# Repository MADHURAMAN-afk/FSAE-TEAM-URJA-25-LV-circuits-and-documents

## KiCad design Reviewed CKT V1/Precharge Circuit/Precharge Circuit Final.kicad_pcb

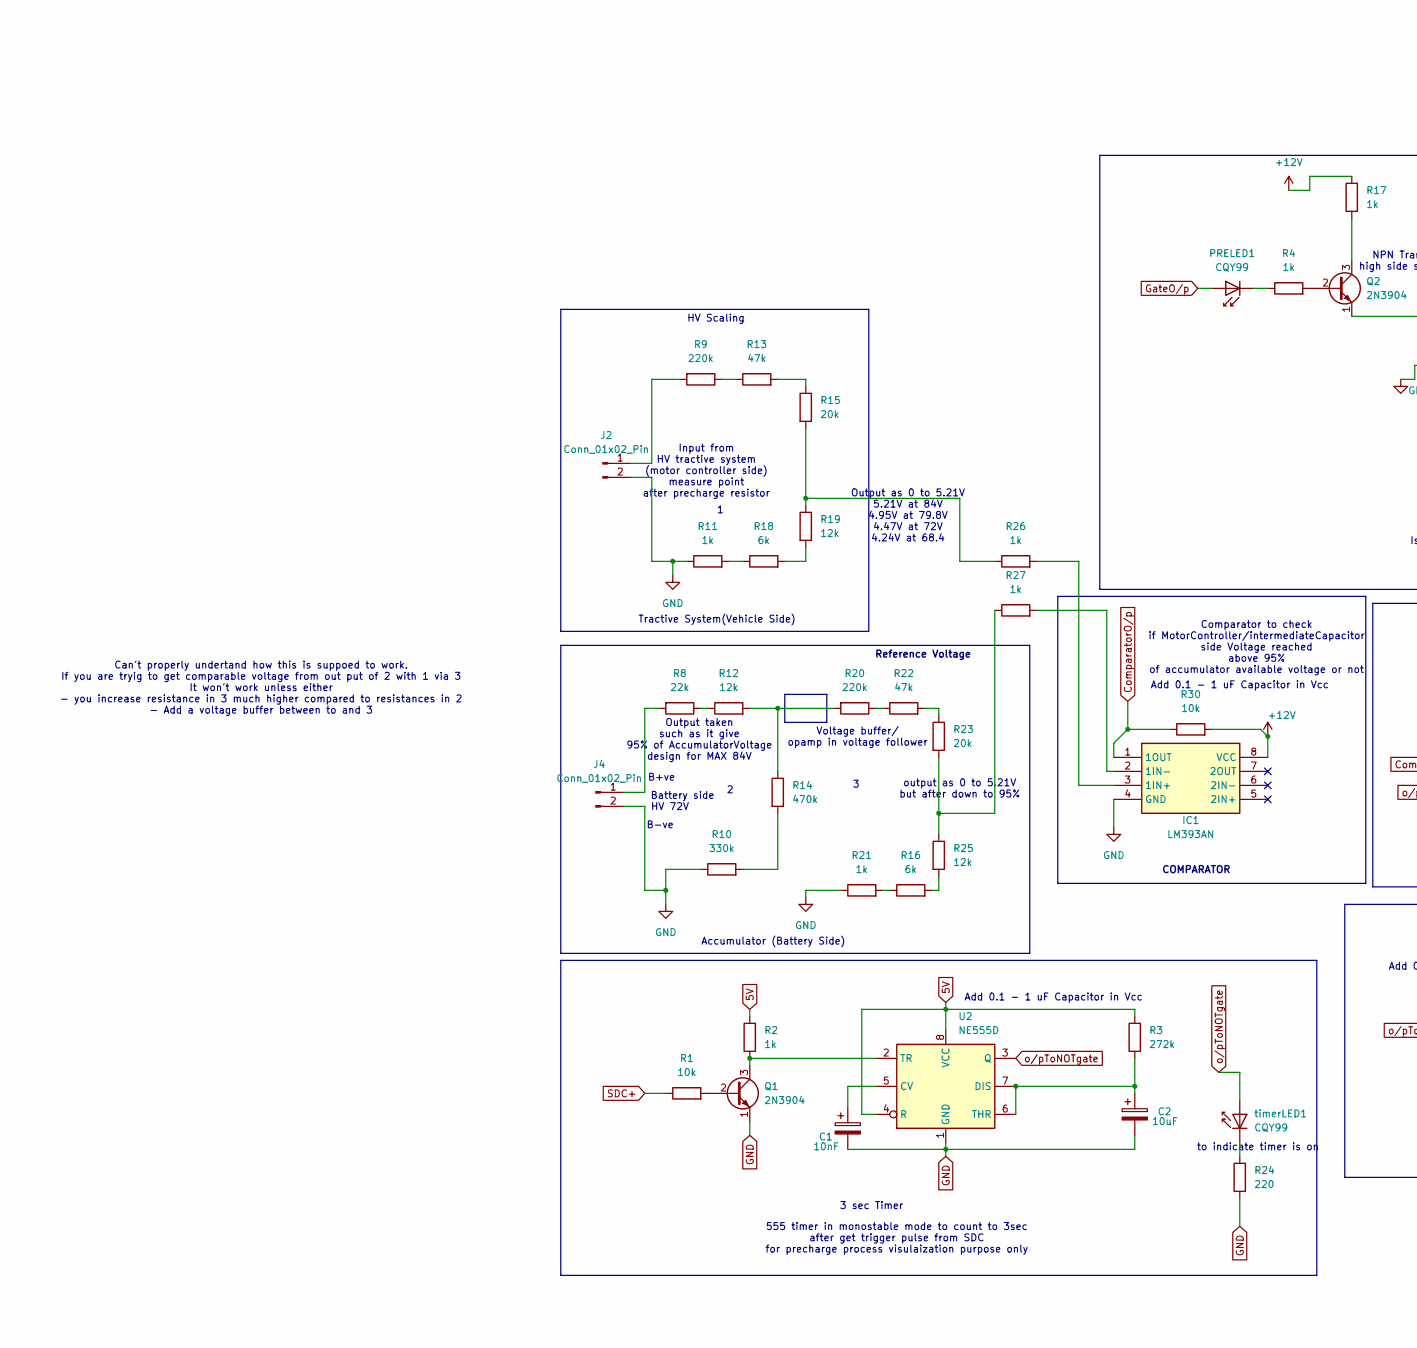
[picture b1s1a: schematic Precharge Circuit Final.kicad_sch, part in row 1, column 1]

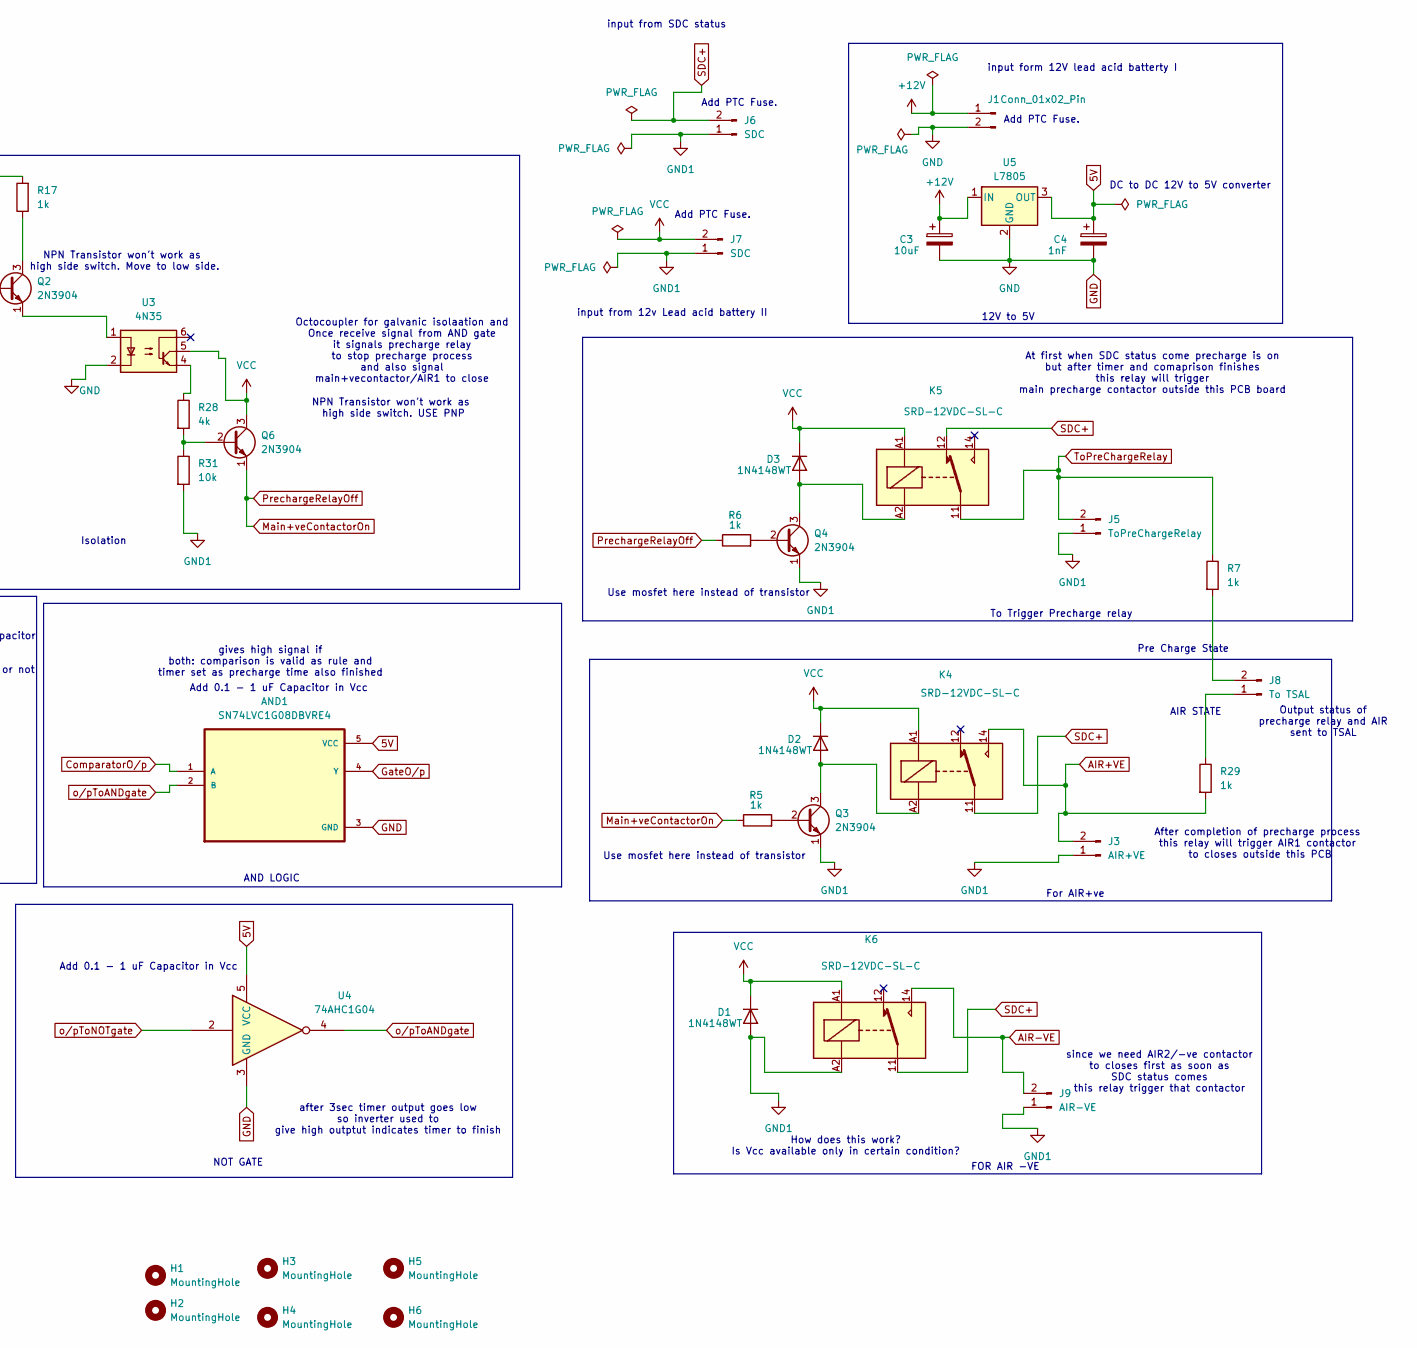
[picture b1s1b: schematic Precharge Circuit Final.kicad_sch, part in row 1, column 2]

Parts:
AND1: SN74LVC1G08DBVRE4; SOT95P280X145-5N
C1: 10nF; CP_Radial_D4.0mm_P2.00mm
C2, C3: 10uF; CP_Radial_D4.0mm_P2.00mm
C4: 1nF; CP_Radial_D4.0mm_P2.00mm
D1, D2, D3: 1N4148WT; D_A-405_P7.62mm_Horizontal
H1, H2, H3, H4, H5, H6: MountingHole; MountingHole_4.3mm_M4
IC1: LM393AN; DIP-8_W7.62mm_Socket; Manufacturer_Part_Number LM393AN; Mouser Part Number N/A
J1, J2, J4: Conn_01x02_Pin; TerminalBlock_Phoenix_MKDS-1,5-2-5.08_1x02_P5.08mm_Horizont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
J3: AIR+VE; TerminalBlock_Phoenix_MKDS-1,5-2-5.08_1x02_P5.08mm_Horizont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
J5: ToPreChargeRelay; TerminalBlock_Phoenix_MKDS-1,5-2-5.08_1x02_P5.08mm_Horizont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
J6, J7: SDC; TerminalBlock_Phoenix_MKDS-1,5-2-5.08_1x02_P5.08mm_Horizont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
J8: To TSAL; TerminalBlock_Phoenix_MKDS-1,5-2-5.08_1x02_P5.08mm_Horizont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
J9: AIR-VE; TerminalBlock_Phoenix_MKDS-1,5-2-5.08_1x02_P5.08mm_Horizont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
K4, K5, K6: SRD-12VDC-SL-C; Relay_SPDT_Hongfa_HF3F-L-xx-1ZL1T
PRELED1: CQY99; LED_D5.0mm_IRGrey
Q1, Q2, Q3, Q4, Q6: 2N3904; TO-92_Inline_Wide
R1, R30, R31: 10k; R_Axial_DIN0207_L6.3mm_D2.5mm_P10.16mm_Horizontal
R2, R4, R5, R6, R7, R11, R17, R21, R26, R27, R29: 1k; R_Axial_DIN0207_L6.3mm_D2.5mm_P10.16mm_Horizontal
R3: 272k; R_Axial_DIN0207_L6.3mm_D2.5mm_P10.16mm_Horizontal
R8: 22k; R_Axial_DIN0207_L6.3mm_D2.5mm_P10.16mm_Horizontal
R9, R20: 220k; R_Axial_DIN0207_L6.3mm_D2.5mm_P10.16mm_Horizontal
R10: 330k; R_Axial_DIN0207_L6.3mm_D2.5mm_P10.16mm_Horizontal
R12, R19, R25: 12k; R_Axial_DIN0207_L6.3mm_D2.5mm_P10.16mm_Horizontal
R13, R22: 47k; R_Axial_DIN0207_L6.3mm_D2.5mm_P10.16mm_Horizontal
R14: 470k; R_Axial_DIN0207_L6.3mm_D2.5mm_P10.16mm_Horizontal
R15, R23: 20k; R_Axial_DIN0207_L6.3mm_D2.5mm_P10.16mm_Horizontal
R16, R18: 6k; R_Axial_DIN0207_L6.3mm_D2.5mm_P10.16mm_Horizontal
R24: 220; R_Axial_DIN0207_L6.3mm_D2.5mm_P10.16mm_Horizontal
R28: 4k; R_Axial_DIN0207_L6.3mm_D2.5mm_P10.16mm_Horizontal
U2: NE555D; DIP-8_W7.62mm
U3: 4N35; DIP-6_W7.62mm
U4: 74AHC1G04; SOT-23-5
U5: L7805; TO-220-3_Vertical
timerLED1: CQY99; LED_D5.0mm_IRGrey

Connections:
5V: AND1.5 (VCC), C4.1, R2.2, R3.2, U2.4 (R), U2.8 (VCC), U4.5 (VCC), U5.3 (OUT)
+12V: C3.1, IC1.8 (VCC), J1.1, R17.2, R30.2, U5.1 (IN)
AIR+VE: J3.2, K4.14, R29.2
AIR-VE: J9.2, K6.14
ComparatorO/p: AND1.1 (A), IC1.1 (1OUT), R30.1
GND: AND1.3 (GND), C1.2, C2.2, C3.2, C4.2, IC1.4 (GND), J1.2, J2.2, J4.2, Q1.1 (E), R10.1, R11.1, R21.1, R24.1, U2.1 (GND), U3.2, U4.3 (GND), U5.2 (GND)
GND1: D1.2 (A), J3.1, J5.1, J6.1, J7.1, J9.1, K6.A2, Q3.1 (E), Q4.1 (E), R31.2
GateO/p: AND1.4 (Y), PRELED1.2 (A)
Main+veContactorOn: Q6.1 (E), R5.1, R6.1
unnamed: D2.2 (A), K4.A2, Q3.3 (C)
unnamed: D3.2 (A), K5.A2, Q4.3 (C)
unnamed: IC1.3 (1IN+), R26.2
unnamed: IC1.2 (1IN-), R27.2
unnamed: J2.1, R9.2
unnamed: J4.1, R8.2
unnamed: J8.1, R29.1
unnamed: J8.2, R7.2
unnamed: PRELED1.1 (K), R4.1
unnamed: Q1.2 (B), R1.2
unnamed: Q1.3 (C), R2.1, U2.2 (TR)
unnamed: Q2.2 (B), R4.2
unnamed: Q2.3 (C), R17.1
unnamed: Q2.1 (E), U3.1
unnamed: Q3.2 (B), R5.2
unnamed: Q4.2 (B), R6.2
unnamed: Q6.2 (B), R28.2, R31.1
unnamed: R10.2, R14.2
unnamed: R11.2, R18.1
unnamed: R8.1, R12.1
unnamed: R12.2, R14.1, R20.2
unnamed: R9.1, R13.1
unnamed: R13.2, R15.1
unnamed: R15.2, R19.1, R26.1
unnamed: R16.1, R21.2
unnamed: R16.2, R25.2
unnamed: R18.2, R19.2
unnamed: R20.1, R22.1
unnamed: R22.2, R23.1
unnamed: R23.2, R25.1, R27.1
unnamed: R28.1, U3.4
unnamed: C1.1, U2.5 (CV)
unnamed: C2.1, R3.1, U2.6 (THR), U2.7 (DIS)
unnamed: R24.2, timerLED1.1 (K)
SDC+: J6.2, K4.11, K5.12, K6.11, R1.1
ToPreChargeRelay: J5.2, K5.11, R7.1
VCC: D1.1 (K), D2.1 (K), D3.1 (K), J7.2, K4.A1, K5.A1, K6.A1, Q6.3 (C), U3.5
o/pToANDgate: AND1.2 (B), U4.4
o/pToNOTgate: U2.3 (Q), U4.2, timerLED1.2 (A)

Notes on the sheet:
since we need AIR2/-ve contactor to closes first as soon as SDC status comes this relay trigger that contactor
B+ve
FOR AIR -VE
After completion of precharge process this relay will trigger AIR1 contactor to closes outside this PCB
Output taken such as it give 95% of AccumulatorVoltage design for MAX 84V
B-ve
Battery side
output as 0 to 5.21V but after down to 95%
Add PTC Fuse.
NPN Transistor won't work as high side switch. USE PNP
COMPARATOR
Output status of precharge relay and AIR sent to TSAL
input from SDC status
NOT GATE
Comparator to check if MotorController/intermediateCapacitor side Voltage reached above 95% of accumulator available voltage or not
Isolation
How does this work? Is Vcc available only in certain condition?
At first when SDC status come precharge is on but after timer and comaprison finishes this relay will trigger main precharge contactor outside this PCB board
NPN Transistor won't work as high side switch. Move to low side.
Use mosfet here instead of transistor
3 sec Timer
after 3sec timer output goes low so inverter used to give high outptut indicates timer to finish
Reference Voltage
Pre Charge State
12V to 5V
555 timer in monostable mode to count to 3sec after get trigger pulse from SDC for precharge process visulaization purpose only
gives high signal if both: comparison is valid as rule and timer set as precharge time also finished
input form 12V lead acid batterty I
Output as 0 to 5.21V 5.21V at 84V 4.95V at 79.8V 4.47V at 72V 4.24V at 68.4
Add 0.1 - 1 uF Capacitor in Vcc
AIR STATE
DC to DC 12V to 5V converter
Tractive System(Vehicle Side)
HV 72V
Octocoupler for galvanic isolaation and Once receive signal from AND gate it signals precharge relay to stop precharge process and also signal main+vecontactor/AIR1 to close
Voltage buffer/ opamp in voltage follower
HV Scaling
Input from HV tractive system (motor controller side) measure point after precharge resistor
For AIR+ve
AND LOGIC

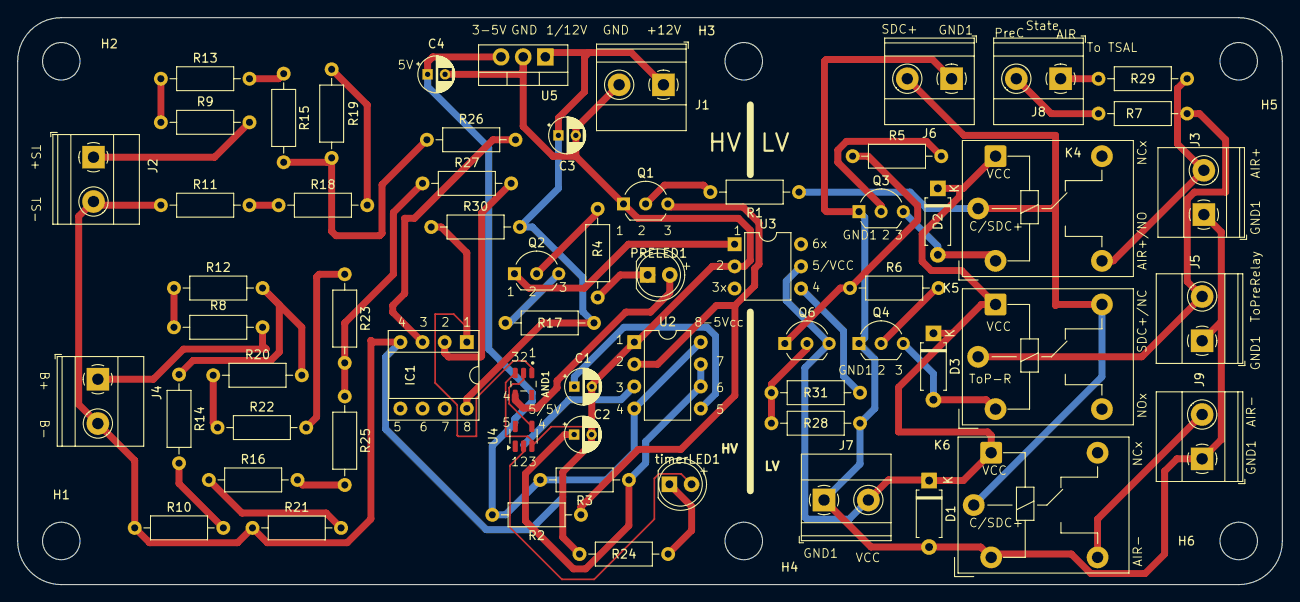
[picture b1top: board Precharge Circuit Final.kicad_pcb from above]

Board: 2 copper layers, 145.0 x 65.0 mm, 69 parts (0 on the bottom side), 48 nets.

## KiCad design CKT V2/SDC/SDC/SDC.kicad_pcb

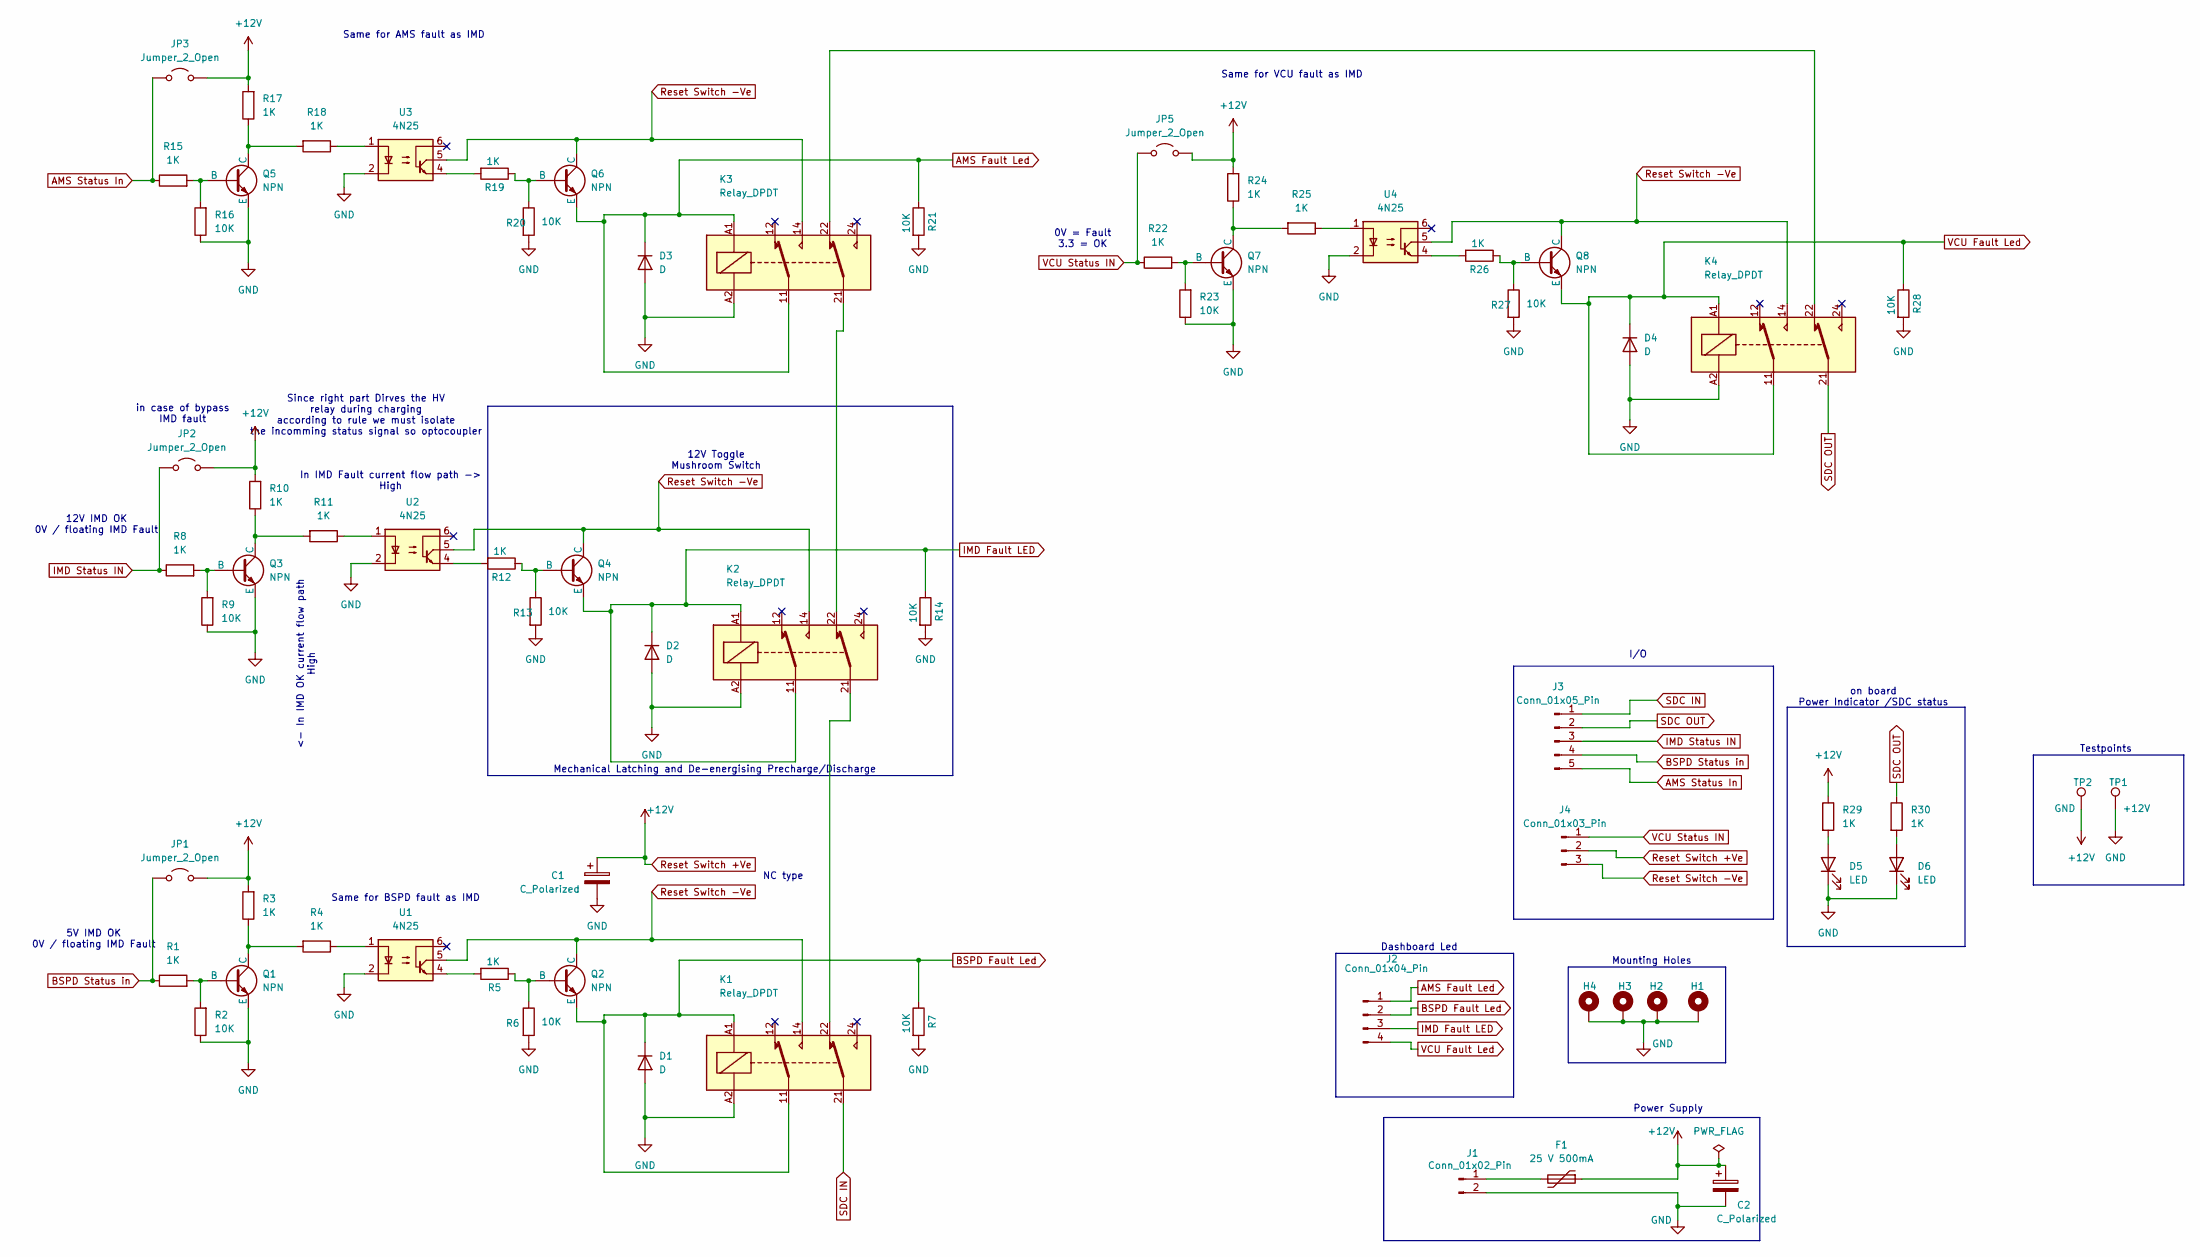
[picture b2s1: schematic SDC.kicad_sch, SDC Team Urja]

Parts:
C1, C2: C_Polarized; CP_Radial_D12.5mm_P7.50mm
D1, D2, D3, D4: D; D_A-405_P7.62mm_Horizontal
D5, D6: LED; LED_D4.0mm
F1: 25 V 500mA; Fuse_BelFuse_0ZRE0008FF_L8.3mm_W3.8mm
H1, H2, H3, H4: MountingHole_Pad; MountingHole_3.2mm_M3_ISO7380_Pad
J1: Conn_01x02_Pin; PinHeader_1x02_P2.54mm_Vertical
J2: Conn_01x04_Pin; PinHeader_1x04_P2.54mm_Vertical
J3: Conn_01x05_Pin; PinHeader_1x05_P2.54mm_Vertical
J4: Conn_01x03_Pin; PinHeader_1x03_P2.54mm_Vertical
JP1, JP2, JP3, JP5: Jumper_2_Open; PinHeader_1x02_P2.54mm_Vertical
K1, K2, K3, K4: Relay_DPDT; Relay_DPDT_Finder_40.52
Q1: NPN; TO-92L_Inline_Wide
Q2, Q3, Q4, Q5, Q6, Q7, Q8: NPN; TO-92_Inline_Wide
R1, R3, R4, R5, R8, R10, R11, R12, R15, R17, R18, R19, R22, R24, R25, R26, R29, R30: 1K; R_Axial_DIN0207_L6.3mm_D2.5mm_P7.62mm_Horizontal
R2, R6, R7, R9, R13, R14, R16, R20, R21, R23, R27, R28: 10K; R_Axial_DIN0207_L6.3mm_D2.5mm_P7.62mm_Horizontal
TP1: +12V; TestPoint_Pad_1.0x1.0mm
TP2: GND; TestPoint_Pad_1.0x1.0mm
U1, U2, U3, U4: 4N25; DIP-6_W7.62mm

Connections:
AMS Fault Led: D3.1 (K), J2.1, K3.11, K3.A1, Q6.3 (E), R21.1
AMS Status In: J3.5, JP3.1 (A), R15.1
BSPD Fault Led: D1.1 (K), J2.2, K1.11, K1.A1, Q2.3 (E), R7.1
BSPD Status in: J3.4, JP1.1 (A), R1.1
GND: C1.2, C2.2, D1.2 (A), D2.2 (A), D3.2 (A), D4.2 (A), D5.1 (K), D6.1 (K), H1.1, H2.1, H3.1, H4.1, J1.2, K1.A2, K2.A2, K3.A2, K4.A2, Q1.3 (E), Q3.3 (E), Q5.3 (E), Q7.3 (E), R2.1, R6.2, R7.2, R9.1, R13.2, R14.2, R16.1, R20.2, R21.2, R23.1, R27.2, R28.2, TP1.1, U1.2, U2.2, U3.2, U4.2
IMD Fault LED: D2.1 (K), J2.3, K2.11, K2.A1, Q4.3 (E), R14.1
IMD Status IN: J3.3, JP2.1 (A), R8.1
unnamed: D5.2 (A), R29.2
unnamed: D6.2 (A), R30.2
unnamed: F1.2, J1.1
unnamed: K1.22, K2.21
unnamed: K2.22, K3.21
unnamed: K3.22, K4.22
unnamed: Q1.2 (B), R1.2, R2.2
unnamed: Q1.1 (C), R3.1, R4.2
unnamed: Q2.2 (B), R5.1, R6.1
unnamed: Q3.2 (B), R8.2, R9.2
unnamed: Q3.1 (C), R10.1, R11.2
unnamed: Q4.2 (B), R12.1, R13.1
unnamed: Q5.2 (B), R15.2, R16.2
unnamed: Q5.1 (C), R17.1, R18.2
unnamed: Q6.2 (B), R19.1, R20.1
unnamed: Q7.2 (B), R22.2, R23.2
unnamed: Q7.1 (C), R24.1, R25.2
unnamed: Q8.2 (B), R26.1, R27.1
unnamed: R4.1, U1.1
unnamed: R5.2, U1.4
unnamed: R11.1, U2.1
unnamed: R12.2, U2.4
unnamed: R18.1, U3.1
unnamed: R19.2, U3.4
unnamed: R25.1, U4.1
unnamed: R26.2, U4.4
Reset Switch +Ve: C1.1, C2.1, F1.1, J4.2, JP1.2 (B), JP2.2 (B), JP3.2 (B), JP5.2 (B), R3.2, R10.2, R17.2, R24.2, R29.1, TP2.1
Reset Switch -Ve: J4.3, K1.14, K2.14, K3.14, K4.14, Q2.1 (C), Q4.1 (C), Q6.1 (C), Q8.1 (C), U1.5, U2.5, U3.5, U4.5
SDC IN: J3.1, K1.21
SDC OUT: J3.2, K4.21, R30.1
VCU Fault Led: D4.1 (K), J2.4, K4.11, K4.A1, Q8.3 (E), R28.1
VCU Status IN: J4.1, JP5.1 (A), R22.1

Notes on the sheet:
NC type
I/O
Dashboard Led
0V = Fault 3.3 = OK
5V IMD OK 0V / floating IMD Fault
Power Supply
12V Toggle Mushroom Switch
Same for VCU fault as IMD
Mounting Holes
on board Power Indicator /SDC status
Since right part Dirves the HV relay during charging according to rule we must isolate the incomming status signal so optocoupler
Testpoints
In IMD Fault current flow path -> High
12V IMD OK 0V / floating IMD Fault
Same for BSPD fault as IMD
Mechanical Latching and De-energising Precharge/Discharge
Same for AMS fault as IMD
<- In IMD OK current flow path High
in case of bypass IMD fault

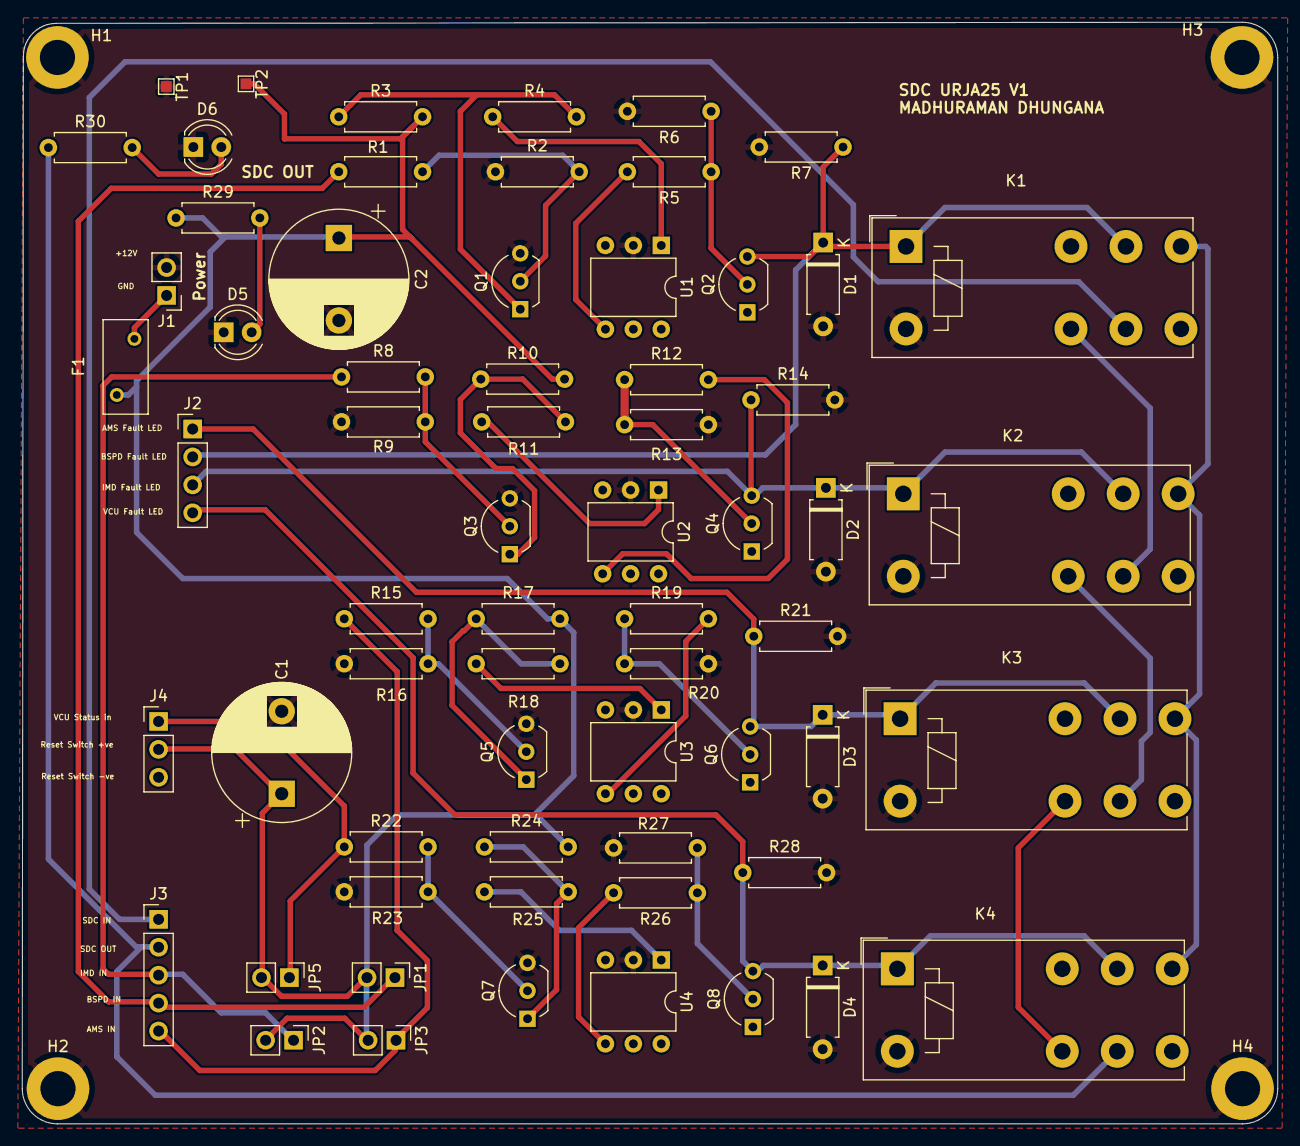
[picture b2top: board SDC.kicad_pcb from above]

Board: 2 copper layers, 114.2 x 100.2 mm, 69 parts (0 on the bottom side), 39 nets.

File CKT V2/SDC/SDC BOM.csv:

Reference,Value,Qty,DNP
"C1,C2",C_Polarized,2,
"D1,D2,D3,D4",D,4,
"D5,D6",LED,2,
F1,25 V 500mA,1,
J1,Conn_01x02_Pin,1,
J2,Conn_01x04_Pin,1,
J3,Conn_01x05_Pin,1,
J4,Conn_01x03_Pin,1,
"JP1,JP2,JP3,JP5",Jumper_2_Open,4,
"K1,K2,K3,K4",Relay_DPDT,4,
"Q1,Q2,Q3,Q4,Q5,Q6,Q7,Q8",NPN,8,
"R1,R3,R4,R5,R8,R10,R11,R12,R15,R17,R18,R19,R22,R24,R25,R26,R29,R30",1K,18,
"R2,R6,R7,R9,R13,R14,R16,R20,R21,R23,R27,R28",10K,12,
TP1,+12V,1,
TP2,GND,1,
"U1,U2,U3,U4",4N25,4,

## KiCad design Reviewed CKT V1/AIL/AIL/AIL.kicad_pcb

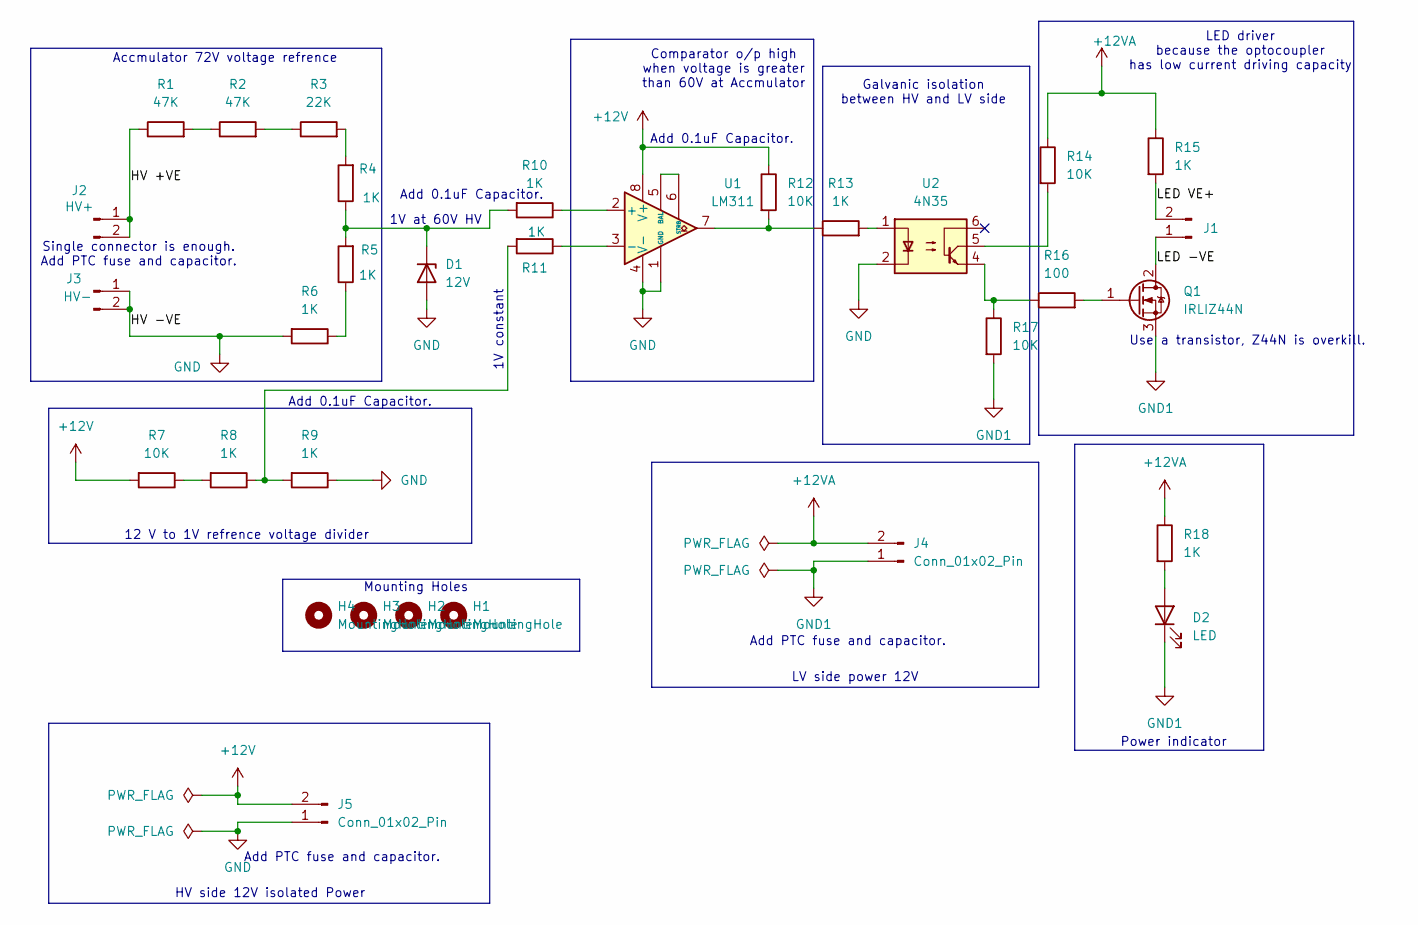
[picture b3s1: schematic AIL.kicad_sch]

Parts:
D1: 12V; D_A-405_P10.16mm_Horizontal
D2: LED; LED_D5.0mm
H1, H2, H3, H4: MountingHole; MountingHole_4.3mm_M4
J1, J4, J5: Conn_01x02_Pin; TerminalBlock_Phoenix_MKDS-1,5-2-5.08_1x02_P5.08mm_Horizont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
J2: HV+; TerminalBlock_Phoenix_MKDS-1,5-2-5.08_1x02_P5.08mm_Horizont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
J3: HV-; TerminalBlock_Phoenix_MKDS-1,5-2-5.08_1x02_P5.08mm_Horizont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
Q1: IRLIZ44N; TO-220F-3_Vertical
R1, R2: 47K; R_Axial_DIN0204_L3.6mm_D1.6mm_P7.62mm_Horizontal
R3: 22K; R_Axial_DIN0204_L3.6mm_D1.6mm_P7.62mm_Horizontal
R4, R5, R6, R8, R9, R10, R11, R13, R15, R18: 1K; R_Axial_DIN0204_L3.6mm_D1.6mm_P7.62mm_Horizontal
R7, R12, R14, R17: 10K; R_Axial_DIN0204_L3.6mm_D1.6mm_P7.62mm_Horizontal
R16: 100; R_Axial_DIN0204_L3.6mm_D1.6mm_P7.62mm_Horizontal
U1: LM311; CERDIP-8_W7.62mm_SideBrazed_LongPads
U2: 4N35; DIP-6_W7.62mm

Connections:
+12V: J5.2, R7.2, R12.1, U1.8 (V+)
+12VA: J4.2, R14.1, R15.1, R18.1
/HV +VE: J2.1, J2.2, R1.1
/LED -VE: J1.1, Q1.2 (D)
/LED VE+: J1.2, R15.2
GND: D1.2 (A), J3.1, J3.2, J5.1, R6.2, R9.1, U1.1 (GND), U1.4 (V-), U2.2
GND1: D2.1 (K), J4.1, Q1.3 (S), R17.2
unnamed: D1.1 (K), R4.1, R5.2, R10.2
unnamed: D2.2 (A), R18.2
unnamed: Q1.1 (G), R16.2
unnamed: R1.2, R2.1
unnamed: R2.2, R3.1
unnamed: R3.2, R4.2
unnamed: R5.1, R6.1
unnamed: R7.1, R8.2
unnamed: R8.1, R9.2, R11.2
unnamed: R12.2, R13.1, U1.7
unnamed: R13.2, U2.1
unnamed: R14.2, U2.5
unnamed: R16.1, R17.1, U2.4
unnamed: R10.1, U1.2 (+)
unnamed: R11.1, U1.3 (-)
unnamed: U1.5 (BAL), U1.6 (STRB)

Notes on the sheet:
12 V to 1V refrence voltage divider
Use a transistor, Z44N is overkill.
Add 0.1uF Capacitor.
1V at 60V HV
Power indicator
Galvanic isolation between HV and LV side
Comparator o/p high when voltage is greater than 60V at Accmulator
Accmulator 72V voltage refrence
Add PTC fuse and capacitor.
1V constant
LV side power 12V
Mounting Holes
HV side 12V isolated Power
Single connector is enough. Add PTC fuse and capacitor.
LED driver because the optocoupler has low current driving capacity

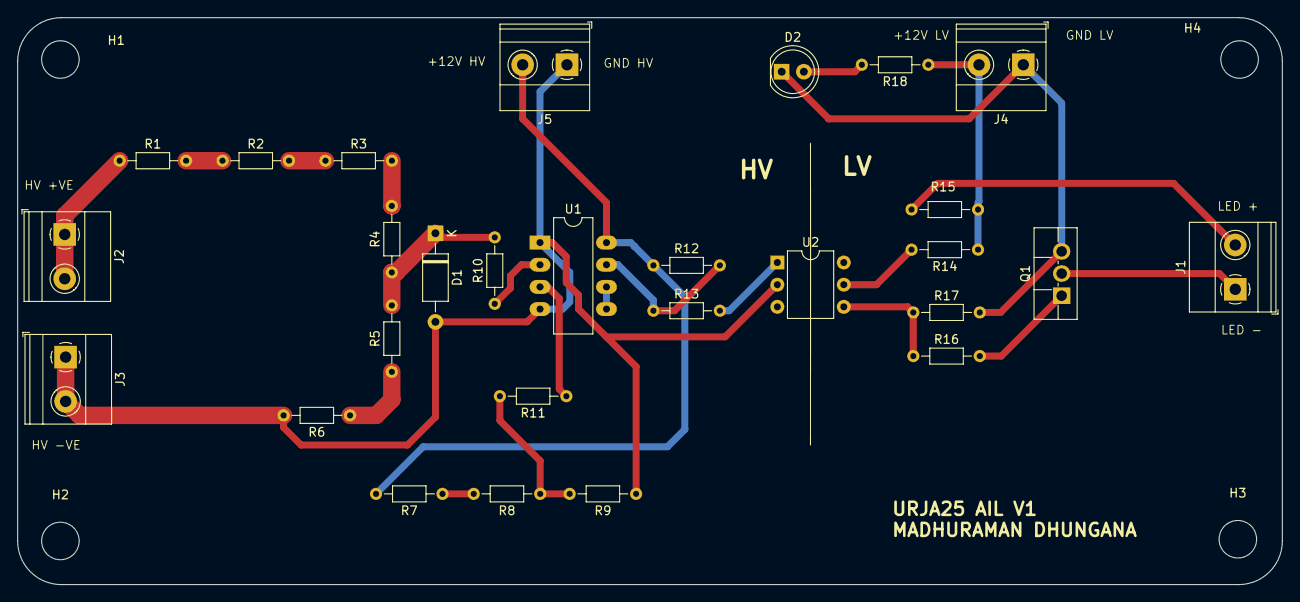
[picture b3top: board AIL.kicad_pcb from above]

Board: 2 copper layers, 145.0 x 65.0 mm, 32 parts (0 on the bottom side), 23 nets.

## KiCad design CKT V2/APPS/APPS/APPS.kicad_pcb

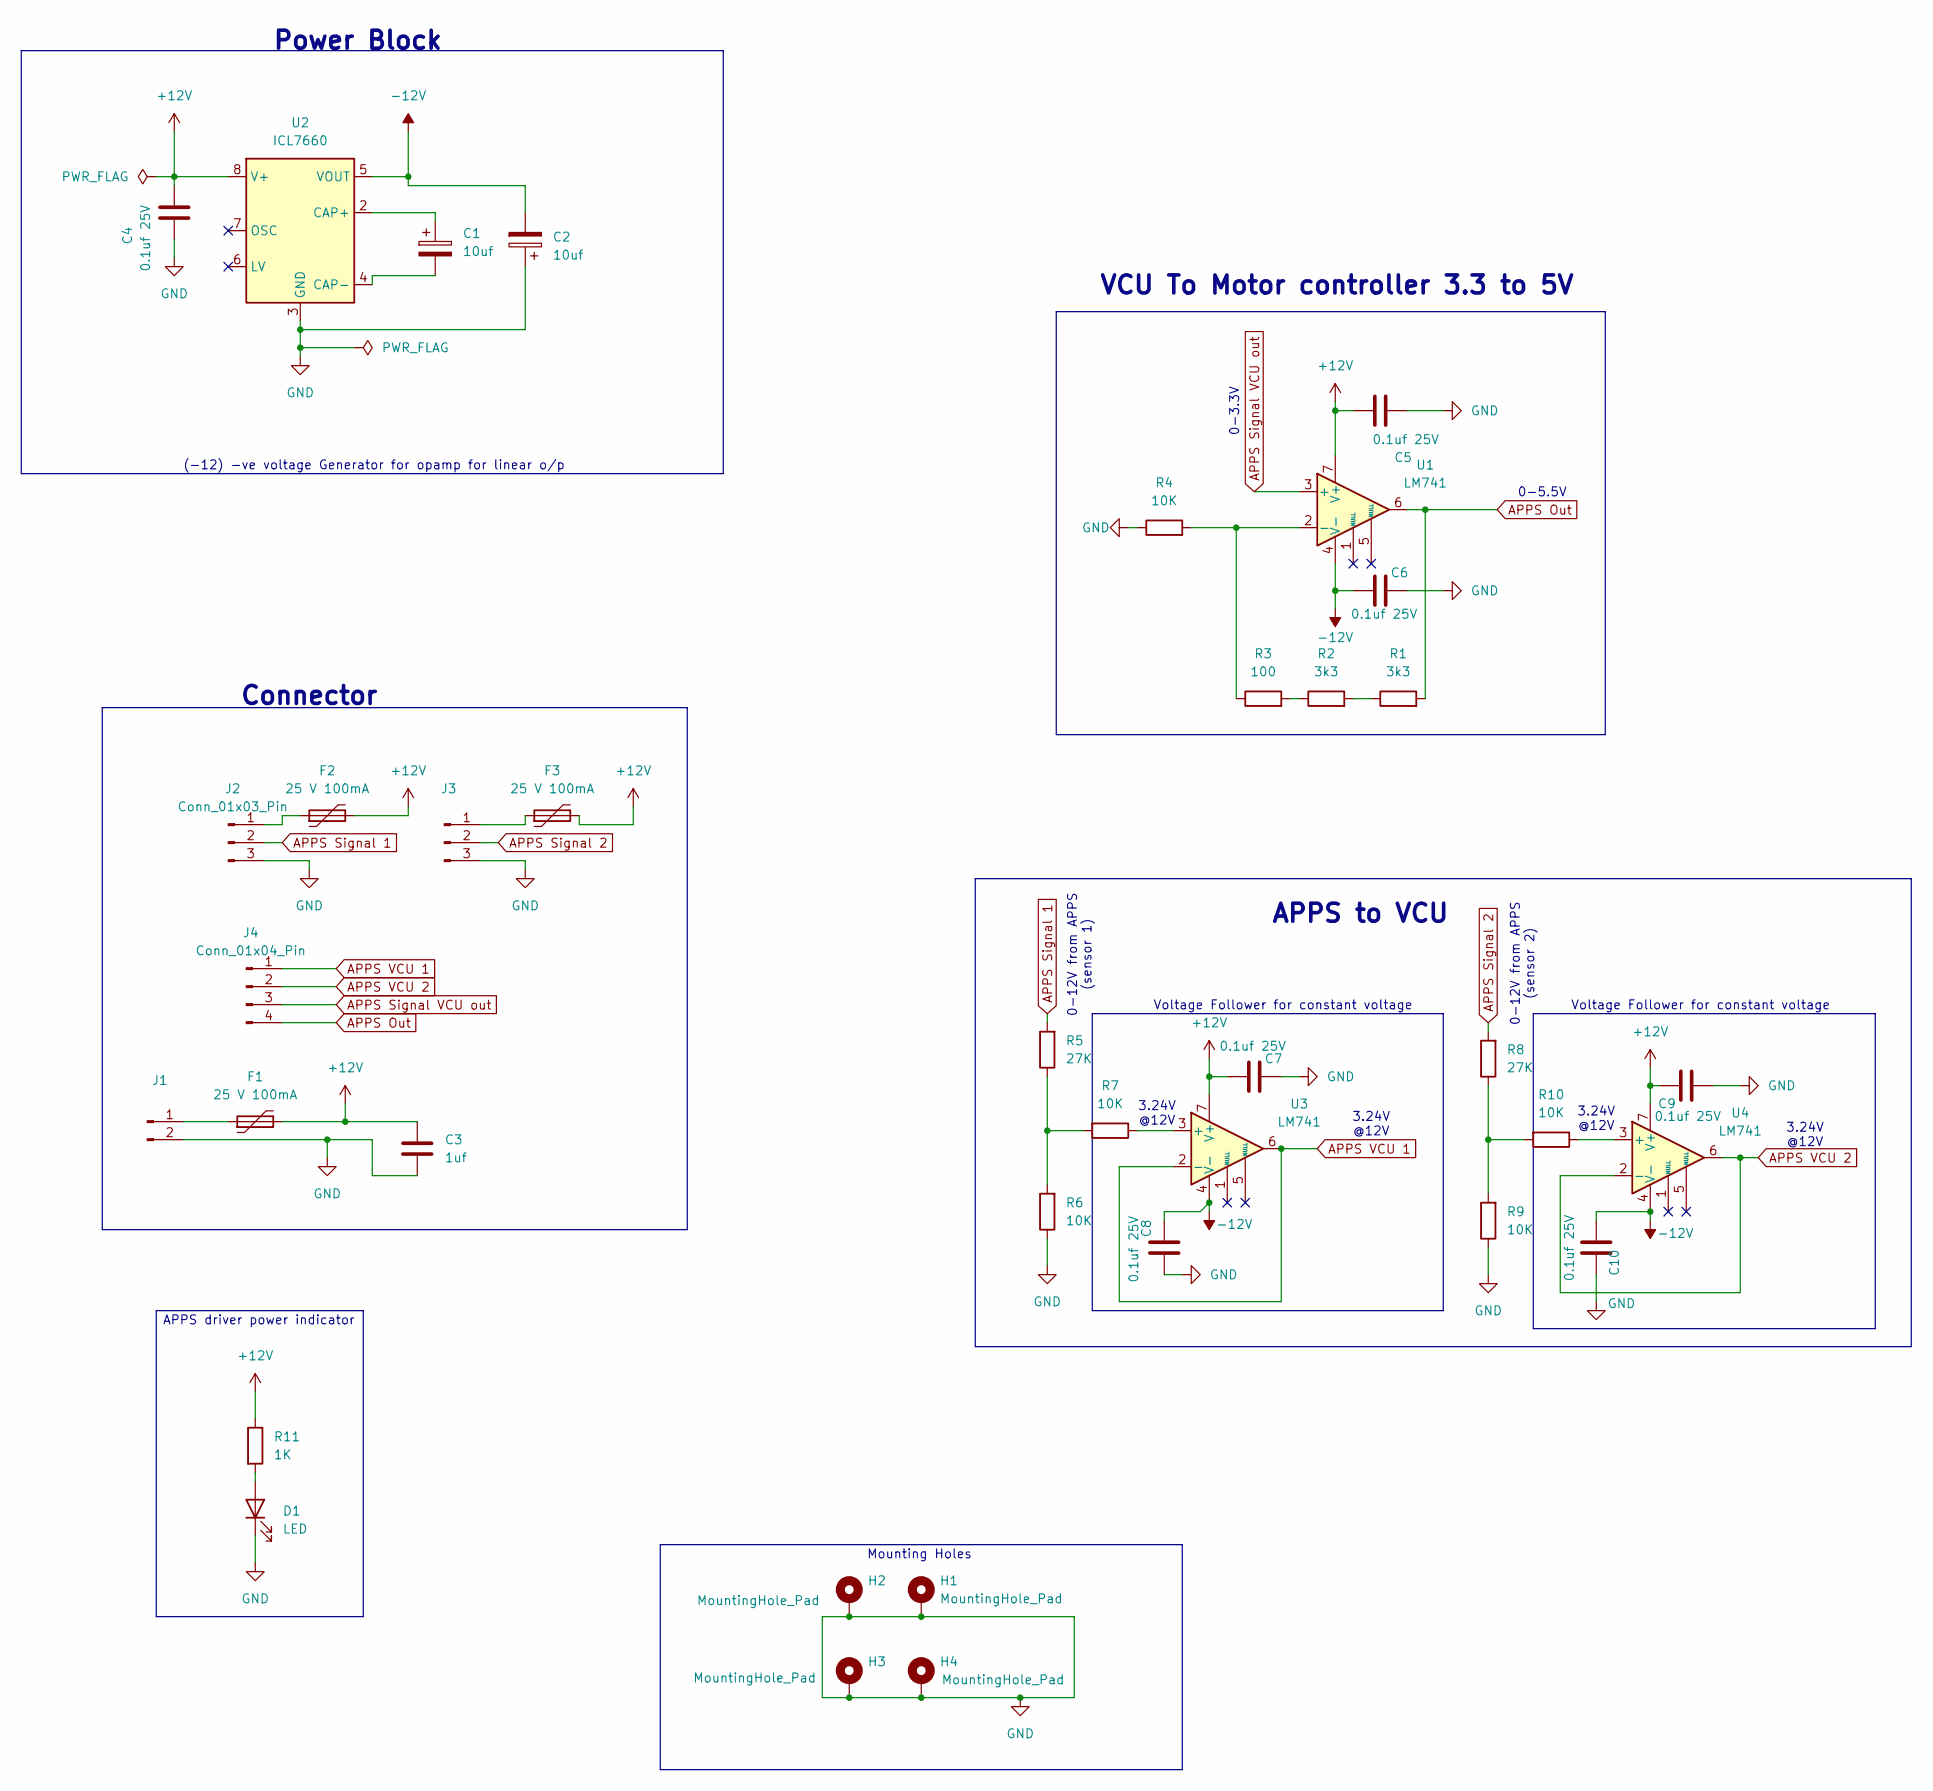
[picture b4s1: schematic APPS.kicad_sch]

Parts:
C1, C2: 10uf; CP_Radial_D8.0mm_P5.00mm
C3: 1uf; CP_Radial_D8.0mm_P5.00mm
C4, C5, C6, C7, C8, C9, C10: 0.1uf 25V; CP_Radial_D8.0mm_P5.00mm
D1: LED; LED_D5.0mm
F1, F2, F3: 25 V 100mA; Fuse_BelFuse_0ZRE0008FF_L8.3mm_W3.8mm
H1, H2, H3, H4: MountingHole_Pad; MountingHole_3.5mm_Pad
J1: Conn_01x02_Pin; PinHeader_1x02_P2.54mm_Vertical
J2, J3: Conn_01x03_Pin; PinHeader_1x03_P2.54mm_Vertical
J4: Conn_01x04_Pin; PinHeader_1x04_P2.54mm_Vertical
R1, R2: 3k3; R_Axial_DIN0207_L6.3mm_D2.5mm_P7.62mm_Horizontal
R3: 100; R_Axial_DIN0207_L6.3mm_D2.5mm_P7.62mm_Horizontal
R4, R6, R7, R9, R10: 10K; R_Axial_DIN0207_L6.3mm_D2.5mm_P7.62mm_Horizontal
R5, R8: 27K; R_Axial_DIN0207_L6.3mm_D2.5mm_P7.62mm_Horizontal
R11: 1K; R_Axial_DIN0207_L6.3mm_D2.5mm_P7.62mm_Horizontal
U1, U3, U4: LM741; CERDIP-8_W7.62mm_SideBrazed_LongPads_Socket
U2: ICL7660; SOIC-8_3.9x4.9mm_P1.27mm

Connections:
+12V: C3.1, C4.1, C5.1, C7.1, C9.2, F1.2, F2.2, F3.2, R11.1, U1.7 (V+), U2.8 (V+), U3.7 (V+), U4.7 (V+)
-12V: C2.2, C6.1, C8.2, C10.1, U1.4 (V-), U2.5 (VOUT), U3.4 (V-), U4.4 (V-)
APPS Out: J4.4, R1.2, U1.6
APPS Signal 1: J2.2, R5.2
APPS Signal 2: J3.2, R8.2
APPS Signal VCU out: J4.3, U1.3 (+)
APPS VCU 1: J4.1, U3.2 (-), U3.6
APPS VCU 2: J4.2, U4.2 (-), U4.6
GND: C2.1, C3.2, C4.2, C5.2, C6.2, C7.2, C8.1, C9.1, C10.2, D1.1 (K), H1.1, H2.1, H3.1, H4.1, J1.2, J2.3, J3.3, R4.1, R6.1, R9.1, U2.3 (GND)
unnamed: D1.2 (A), R11.2
unnamed: F1.1, J1.1
unnamed: F2.1, J2.1
unnamed: F3.1, J3.1
unnamed: R1.1, R2.2
unnamed: R2.1, R3.2
unnamed: R5.1, R6.2, R7.2
unnamed: R8.1, R9.2, R10.2
unnamed: R3.1, R4.2, U1.2 (-)
unnamed: C1.1, U2.2 (CAP+)
unnamed: C1.2, U2.4 (CAP-)
unnamed: R7.1, U3.3 (+)
unnamed: R10.1, U4.3 (+)

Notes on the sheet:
APPS to VCU
0-5.5V
0-12V from APPS (sensor 2)
VCU To Motor controller 3.3 to 5V
APPS driver power indicator
3.24V @12V
0-3.3V
(-12) -ve voltage Generator for opamp for linear o/p
Mounting Holes
Power Block
Voltage Follower for constant voltage
Connector
0-12V from APPS (sensor 1)
